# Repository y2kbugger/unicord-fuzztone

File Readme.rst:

Research:
https://www.diystompboxes.com/smfforum/index.php?topic=94633.0

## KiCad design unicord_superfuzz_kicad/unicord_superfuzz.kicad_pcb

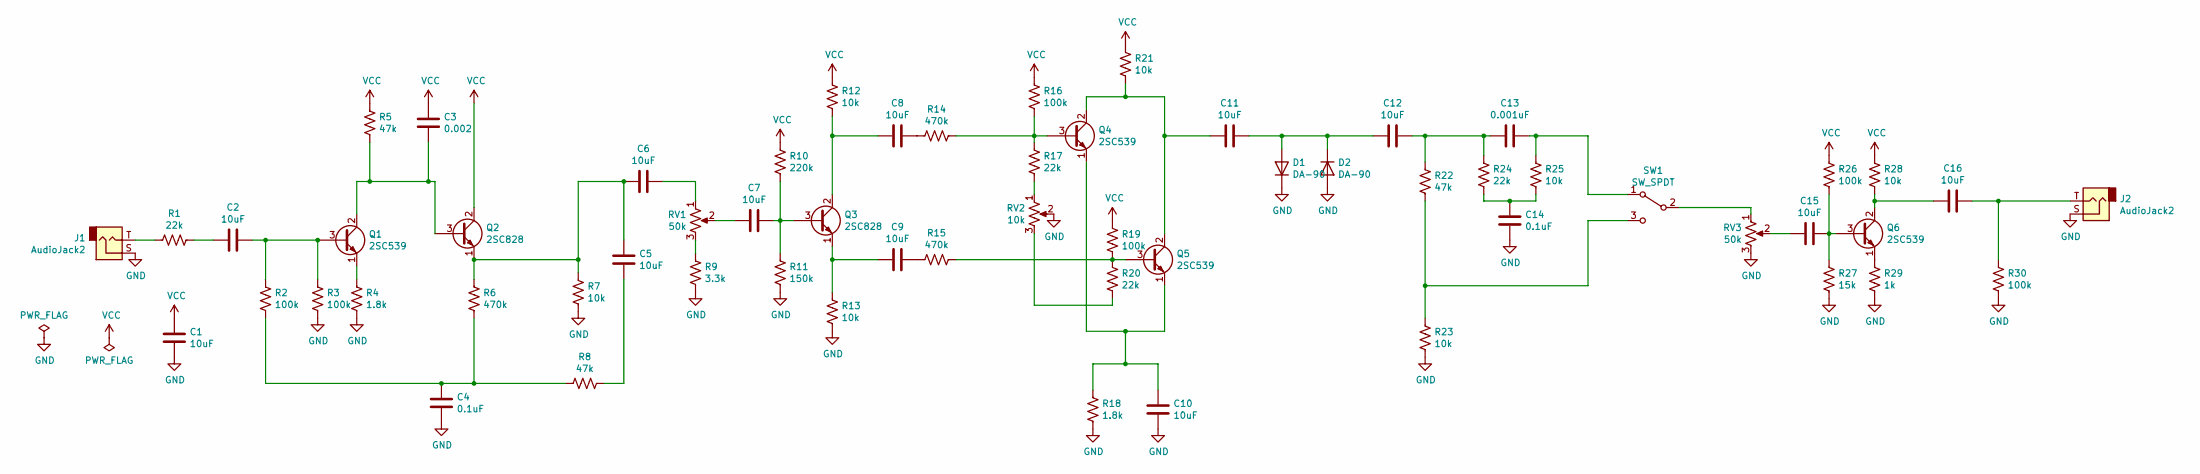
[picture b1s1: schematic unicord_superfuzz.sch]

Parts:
C1, C2, C5, C6, C7, C8, C9, C10, C11, C12, C15, C16: 10uF; C_Radial_D5.0mm_H11.0mm_P2.00mm
C3: 0.002; C_Disc_D5.0mm_W2.5mm_P5.00mm
C4, C14: 0.1uF; C_Disc_D5.0mm_W2.5mm_P5.00mm
C13: 0.001uF; C_Disc_D5.0mm_W2.5mm_P5.00mm
D1, D2: DA-90; D_A-405_P12.70mm_Horizontal
J1, J2: AudioJack2; PinHeader_1x02_P2.54mm_Vertical
Q1, Q4, Q5, Q6: 2SC539; TO-92
Q2, Q3: 2SC828; TO-92
R1, R17, R20, R24: 22k; R_Axial_DIN0204_L3.6mm_D1.6mm_P7.62mm_Horizontal
R2, R3, R16, R19, R26, R30: 100k; R_Axial_DIN0204_L3.6mm_D1.6mm_P7.62mm_Horizontal
R4, R18: 1.8k; R_Axial_DIN0204_L3.6mm_D1.6mm_P7.62mm_Horizontal
R5, R8, R22: 47k; R_Axial_DIN0204_L3.6mm_D1.6mm_P7.62mm_Horizontal
R6, R14, R15: 470k; R_Axial_DIN0204_L3.6mm_D1.6mm_P7.62mm_Horizontal
R7, R12, R13, R21, R23, R25, R28: 10k; R_Axial_DIN0204_L3.6mm_D1.6mm_P7.62mm_Horizontal
R9: 3.3k; R_Axial_DIN0204_L3.6mm_D1.6mm_P7.62mm_Horizontal
R10: 220k; R_Axial_DIN0204_L3.6mm_D1.6mm_P7.62mm_Horizontal
R11: 150k; R_Axial_DIN0204_L3.6mm_D1.6mm_P7.62mm_Horizontal
R27: 15k; R_Axial_DIN0204_L3.6mm_D1.6mm_P7.62mm_Horizontal
R29: 1k; R_Axial_DIN0204_L3.6mm_D1.6mm_P7.62mm_Horizontal
RV1, RV3: 50k; PinHeader_1x03_P2.54mm_Vertical
RV2: 10k; Potentiometer_Vishay_43_Horizontal
SW1: SW_SPDT; PinHeader_1x03_P2.54mm_Vertical

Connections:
GND: C1.2, C4.2, C10.2, C14.2, D1.1 (K), D2.2 (A), J1.S, J2.S, R3.2, R4.2, R7.2, R9.2, R11.2, R13.2, R18.2, R23.2, R27.2, R29.2, R30.2, RV2.2, RV3.3
unnamed: C2.1, Q1.3 (B), R2.1, R3.1
unnamed: C2.2, R1.1
unnamed: C3.2, Q1.2 (C), Q2.3 (B), R5.2
unnamed: C4.1, R2.2, R6.2, R8.2
unnamed: C5.1, C6.2, Q2.1 (E), R6.1, R7.1
unnamed: C5.2, R8.1
unnamed: C6.1, RV1.1
unnamed: C7.1, Q3.3 (B), R10.2, R11.1
unnamed: C7.2, RV1.2
unnamed: C8.1, R14.2
unnamed: C8.2, Q3.2 (C), R12.2
unnamed: C9.1, R15.2
unnamed: C9.2, Q3.1 (E), R13.1
unnamed: C10.1, Q4.1 (E), Q5.1 (E), R18.1
unnamed: C11.1, C12.2, D1.2 (A), D2.1 (K)
unnamed: C11.2, Q4.2 (C), Q5.2 (C), R21.2
unnamed: C12.1, C13.2, R22.1, R24.1
unnamed: C13.1, R25.1, SW1.1 (A)
unnamed: C14.1, R24.2, R25.2
unnamed: C15.1, Q6.3 (B), R26.2, R27.1
unnamed: C15.2, RV3.2
unnamed: C16.1, J2.T, R30.1
unnamed: C16.2, Q6.2 (C), R28.2
unnamed: J1.T, R1.2
unnamed: Q1.1 (E), R4.1
unnamed: Q4.3 (B), R14.1, R16.2, R17.1
unnamed: Q5.3 (B), R15.1, R19.2, R20.1
unnamed: Q6.1 (E), R29.1
unnamed: R9.1, RV1.3
unnamed: R17.2, RV2.1
unnamed: R20.2, RV2.3
unnamed: R22.2, R23.1, SW1.3 (C)
unnamed: RV3.1, SW1.2 (B)
VCC: C1.1, C3.1, Q2.2 (C), R5.1, R10.1, R12.1, R16.1, R19.1, R21.1, R26.1, R28.1

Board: 2 copper layers, 60 parts (0 on the bottom side), 35 nets, no tracks yet.

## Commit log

2020-05-18 Add values for most circuit elements
    Have not yet added anything for transistors, switch, power supply.
2020-05-18 Add power/ground to circuit
2020-05-18 Add annotations to circuit elements
2020-05-18 Add footprints and .net file
2020-05-18 Add bom.csv to project
2020-05-18 Add .gitignore and initial PCB file
2020-05-30 Add research
2020-08-05 Add my research links
2020-08-09 Simulation models added
